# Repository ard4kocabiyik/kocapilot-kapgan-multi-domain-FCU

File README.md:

# Kocapilot Kapgan — Donanım Senkronizasyonlu Uçuş Kontrol Kartı

Kapgan; açık kaynak otopilot yazılımını çalıştıran mikrodenetleyicili uçuş kontrolcüsünü ve Linux tabanlı yardımcı bilgisayarı (YB) tek kart yığınında birleştiren, iki saati ayrılmış bir donanım senkron hattıyla ilişkilendiren bir uçuş kontrol kartıdır. Amaç, İHA'da kaydedilen video karelerini uçuş telemetrisiyle (konum, irtifa, yönelim) milisaniyenin altına yakın doğrulukla eşlemek ve bu doğruluğu kamera görüş alanındaki bir LED ile ölçerek raporlamaktır.

Bu depo, TÜBİTAK 2209-A (2026 yılı 1. dönem) başvurusuna konu olan projenin tasarım dosyalarını, devre benzetim modellerini ve teknik raporlarını içerir.

> **Durum (Kasım 2026):** Rev-A şeması ve 4 katmanlı PCB yerleşimi tamamlandı; güç ağı ve SPI sinyal bütünlüğü benzetimleri yapıldı. Rev-A henüz üretilmedi. Ölçüm ve uçuş sonuçları proje süresince bu depoya eklenecektir.

---

## Depo içeriği

| Klasör / dosya | İçerik |
|---|---|
| `.kicad_pro`, `.kicad_sch`, `.kicad_pcb` | KiCad proje, şema ve PCB dosyaları (Rev-A) |
| `ibom.html` | Etkileşimli malzeme listesi; tarayıcıda açılır, dizgi sırasında kullanılır |
| `kocapilot Kapgan.step` | Kartın 3B modeli |
| `kapgan_case.step` | Kartın kutu modeli |
| `Ltspice/Kapgan_Guc_Agi.asc` | Güç ağı benzetimi (5 V giriş, 3,3 V regülatör açılışı) |
| `Ltspice/Kapgan_SPI_SI.asc` | Mikrodenetleyici–IMU SPI hattı sinyal bütünlüğü benzetimi |
| `Docs/Kocapilot_Kapgan_SCH_Raporu.pdf` | Şema tasarım ve inceleme raporu |
| `Docs/Kapgan_Guc_Agi_Simulasyon_Raporu.pdf` | Güç ağı benzetim raporu |
| `Docs/Kapgan_SPI_SI_Simulasyon_Raporu.pdf` | SPI sinyal bütünlüğü benzetim raporu |
| `Docs/Literatür-Taraması.pdf` | Literatür taraması |

## Kart özeti

- 168 MHz, FPU'lu ARM Cortex-M4F çekirdekli 32-bit mikrodenetleyici
- Ayrı SPI hatlarında, farklı üreticilere ait iki adet 6 eksenli MEMS IMU
- I2C arayüzlü MEMS barometrik basınç sensörü
- SPI üzerinden microSD kayıt, CAN alıcı-verici, motor çıkışları
- Linux tabanlı tek kartlı bilgisayara (YB) takılan 40 pinli genişleme bağlantısı
- 4 katmanlı baskı devre kartı
- Besleme: harici 5 V ve USB-C girişleri diyotla birleştirilir; sensör beslemeleri ferrit boncuklarla dijital hattan ayrılır
- YB ile kart arasındaki seri hat ve senkron hattı tampon entegrelerinden geçer; YB kapalıyken bu hatlar yüksek empedansa geçer
- Uçuş kontrolü ayrı mikrodenetleyicide çalıştığı için kart, YB takılı olmadan da otopilot olarak çalışır

## Senkronizasyon yöntemi

1. Mikrodenetleyici, otopilot yazılımının kamera tetikleme işlevi üzerinden saniyede bir senkron darbesi üretir.
2. Aynı darbe, kesme destekli bir geri besleme girişine geri bağlanır; otopilot yazılımı darbenin kendi saatine göre zamanını kaydeder ve MAVLink `CAMERA_FEEDBACK` mesajıyla YB'ye gönderir.
3. YB, darbenin yükselen kenarını Linux GPIO karakter aygıtı arayüzüyle kendi saatine göre zaman damgalar.
4. Darbe çiftlerinden iki saat arasındaki fark ve kayma (sabit fark + doğrusal kayma modeli) kestirilir; her video karesinin zamanı uçuş kontrolcüsü saatine çevrilerek konum ve yönelim ara değerlemeyle bulunur.

Otopilot yazılımının kaynak kodu değiştirilmez; yalnızca kart tanım dosyaları ve parametreler kullanılır.

Eşleme doğruluğu üç yöntemle karşılaştırılır: **K1** telemetri mesajının YB'ye varış zamanı, **K2** yalnızca MAVLink zaman eşleme protokolü, **K3** protokol + donanım senkron darbesi (önerilen yöntem). Gerçek değer, kamera görüş alanındaki ve pin kenarından zaman damgalanan bir LED ile ölçülür.

## Benzetim sonuçları (özet)

| Benzetim | Sonuç |
|---|---|
| Güç ağı | 3,3 V hattı aşım olmadan yaklaşık 3 ms'de oturuyor; açılış tepe akımları sigorta tutma akımlarının altında |
| SPI sinyal bütünlüğü | Örneklenen tüm bitler lojik eşikleri sağlıyor |

Ayrıntılar `Docs/` klasöründeki raporlardadır. Benzetim sonuçları Rev-A üzerinde osiloskop ölçümleriyle karşılaştırılacaktır.

## Yol haritası

| İş paketi | Kapsam |
|---|---|
| İP1 | Rev-A üretimi, dizgi, ilk enerji; kart tanım dosyaları ve otopilot yazılımının yüklenmesi |
| İP2 | YB kayıt servisi, senkron darbesi, saat modeli ve eşleme yazılımı |
| İP3 | Elektriksel ölçümler, tetik gecikmesi ölçümü, masaüstü senkron deneyleri (K1–K3), Rev-B tasarımı |
| İP4 | Rev-B üretimi, uçuş platformunun kurulumu, pervanesiz ve iple bağlı testler |
| İP5 | Pilot kontrolünde, görerek yapılan uçuşlar ve uçuş içi senkron ölçümleri |
| İP6 | İstatistiksel analiz ve veri setinin yayımlanması |

## Ekip

- Arda Kocabıyık — proje yürütücüsü
- Ali Demirci
- Efe Haskuka

Akademik danışman: Sibel Yenikaya — Bursa Uludağ Üniversitesi, Elektrik-Elektronik Mühendisliği Bölümü

## Atıf

A. Kocabıyık, A. Demirci ve E. Haskuka, "Uçuş kontrol kartı tasarım dosyaları, devre benzetim modelleri ve teknik raporlar," GitHub deposu, 2026. https://github.com/ard4kocabiyik/kocapilot-kapgan-multi-domain-FCU

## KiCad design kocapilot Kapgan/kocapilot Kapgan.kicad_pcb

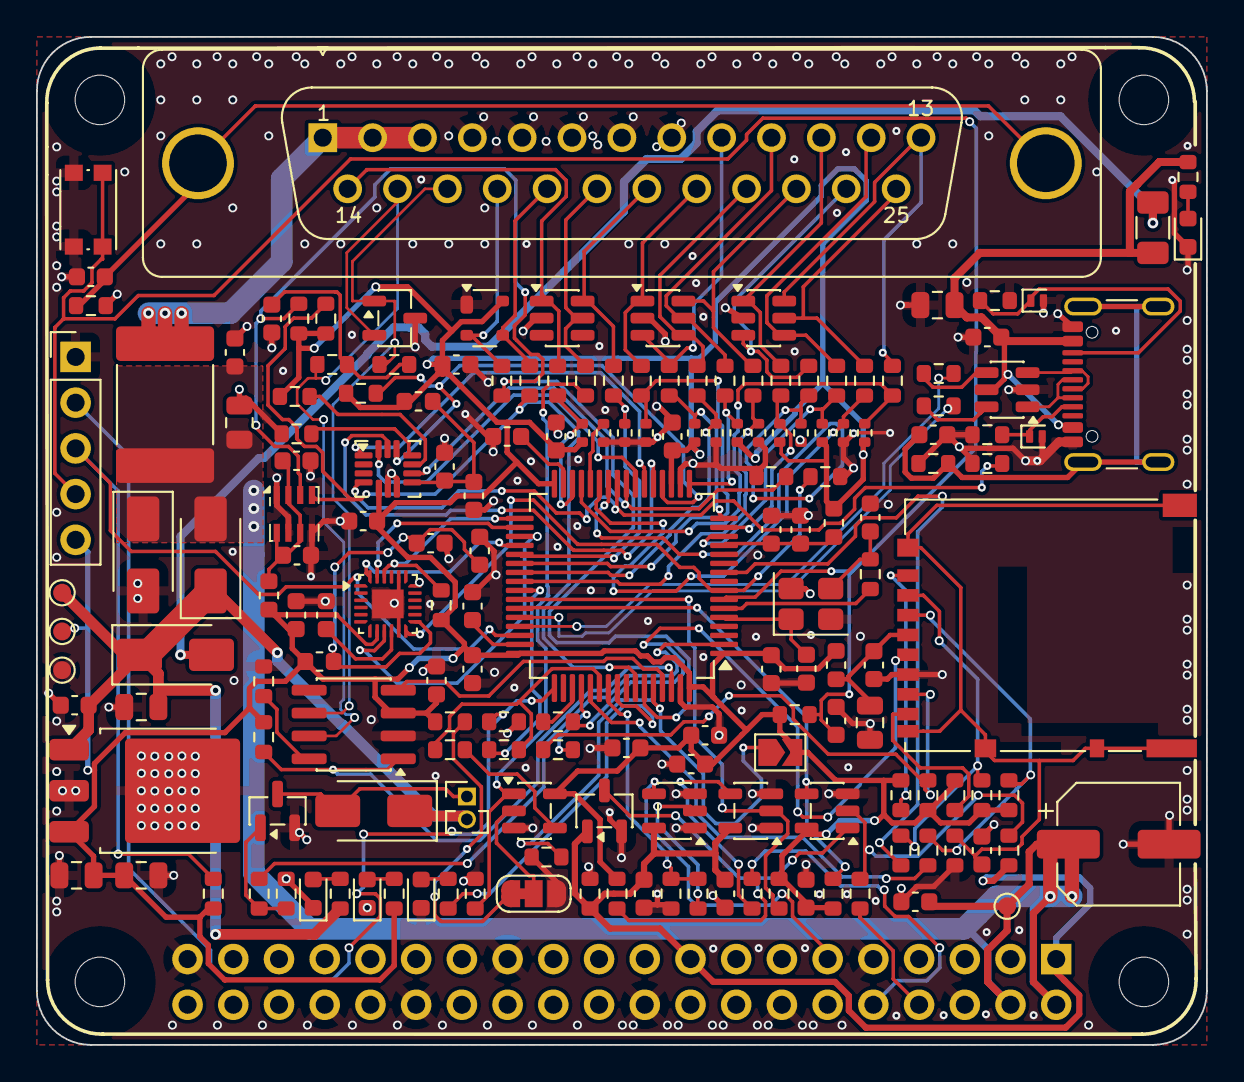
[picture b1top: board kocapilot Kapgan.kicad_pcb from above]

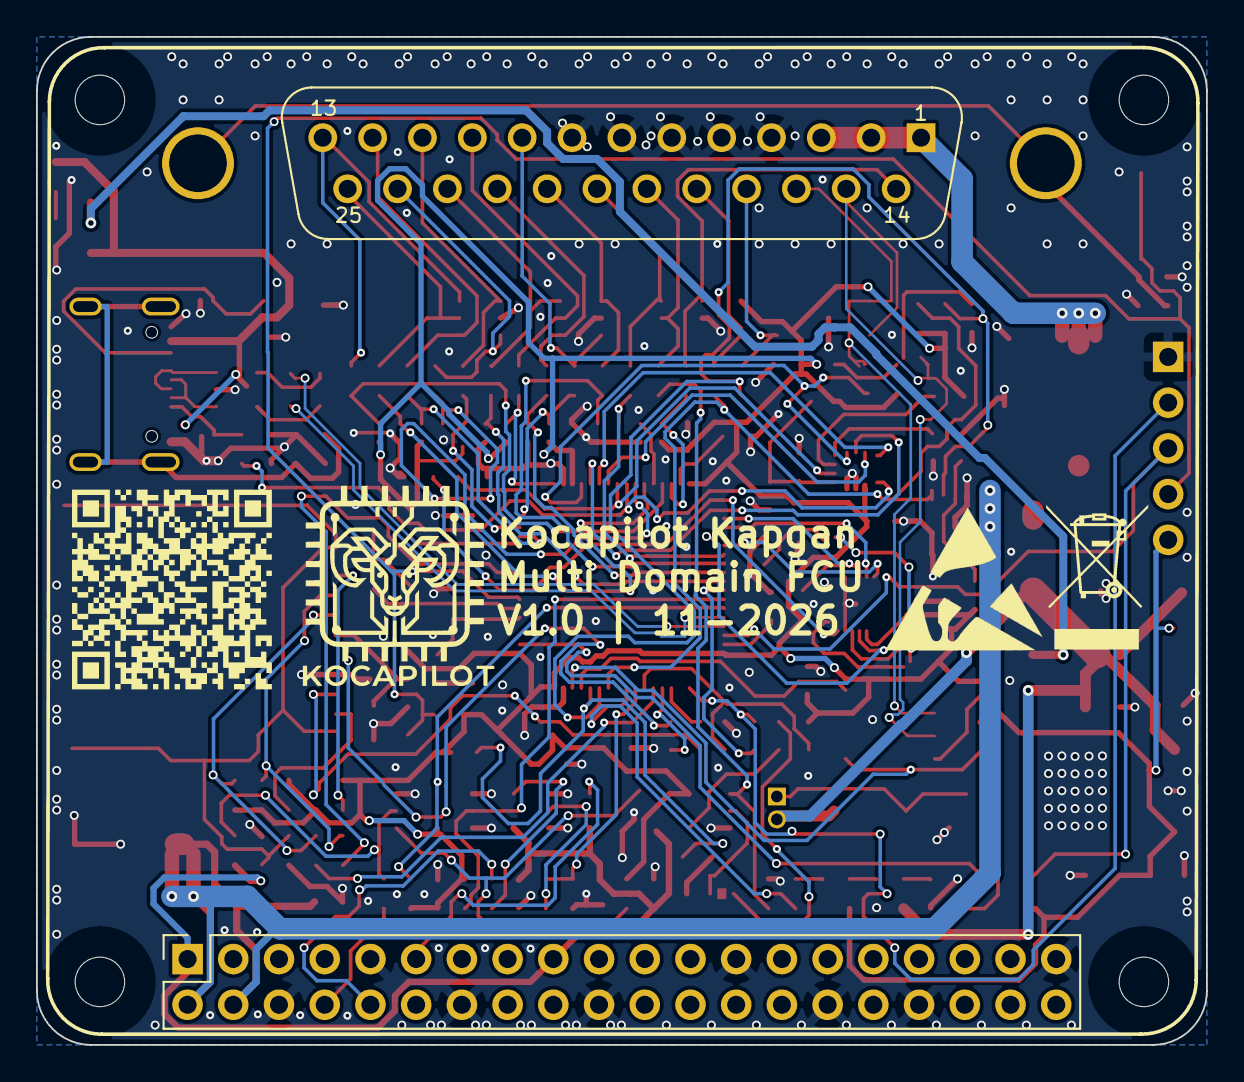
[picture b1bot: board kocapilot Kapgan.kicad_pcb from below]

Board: 4 copper layers, 65.0 x 56.0 mm, 181 parts (4 on the bottom side), 117 nets.

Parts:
C1, C2, C37, C43: 4.7n; C_0603_1608Metric
C3, C5, C7, C10, C11, C12, C14, C16, C18, C20, C21, C22, C23, C24, C25, C27, C28, C30, C31, C33, C34, C35, C40, C42, C44: 0.1u; C_0603_1608Metric
C4, C29: 4.7u; C_0805_2012Metric
C6, C8, C9, C38: 10u; C_0805_2012Metric
C13, C17, C36: 1u; C_0603_1608Metric
C15, C19: 2.2U; C_0603_1608Metric
C26: 10n; C_0603_1608Metric
C32, C39: 12p; C_0603_1608Metric
C41: 100u/16v; CP_Elec_6.3x5.4
CR1: PESD2CAN_215; SOT-23-3
D1: SMAJ6.0A; D_SMA
D2, D3, D7: SS34; D_SMA
D4, D6, D13: ESDA6V1-5SC6; SOT-23-6
D5: PRTR5V0U2X; SOT-143
D8: LED_RED_5V; LED_0603_1608Metric
D9: LED_BLUE_STATUS; LED_0603_1608Metric
D10: LED_GREEN_3V3; LED_0603_1608Metric
D11: LED_AMBER_VBUS; LED_0603_1608Metric
D12, D14: PESD5V0S1UL; D_SOD-882
F1: 2A PTC; Fuse_2920_7451Metric
F2: 1A PTC; Fuse_1206_3216Metric
FB1, FB2, FB3, FB4, FB5: BLM18EG601SN1D; L_0603_1608Metric
H1, H2, H3, H4: M2.5_Mount; MountingHole_2.75mm_M2.5_HAT
J1: SWD; PinHeader_1x05_P2.54mm_Vertical
J2: DB25_Pins_MountingHoles; DSUB-25_Pins_Vertical_P2.77x2.84mm_MountingHoles
J3: Conn_01x02_Pin; PinHeader_1x02_P1.27mm_Vertical
J4: USB_C_Receptacle_USB2.0_16P; USB_C_Receptacle_GCT_USB4105-xx-A_16P_TopMnt_Horizontal
J5: Micro_SD_Card; microSD_HC_Hirose_DM3AT-SF-PEJM5
J6: Raspberry_Pi_Zero_2W; PinSocket_2x20_P2.54mm_Vertical
JP1: SolderJumper_3_Bridged12; SolderJumper-3_P1.3mm_Bridged12_RoundedPad1.0x1.5mm_NumberL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
JP2: SolderJumper_2_Open; SolderJumper-2_P1.3mm_Open_TrianglePad1.0x1.5mm
LOGO0: ESD-Logo_8.9x8mm_SilkScreen
LOGO1: WEEE-Logo_5.6x8mm_SilkScreen
Q1: AO3400A; SOT-23
Q2: 2N7002; SOT-23-3
R1, R61, R72: 1M; R_0603_1608Metric
R2: 0; R_0603_1608Metric
R3, R16: 2.2K; R_0603_1608Metric
R4, R6, R7, R10, R14, R18, R27, R29, R33, R35, R38, R53, R54, R62, R65, R69, R70, R73, R75, R78, R80: 10K; R_0603_1608Metric
R5, R15: 1K; R_0603_1608Metric
R8, R28: 60.4; R_0603_1608Metric
R9, R34, R47, R79: 100; R_0603_1608Metric
R11: 0_DNP; R_0603_1608Metric
R12, R19, R20, R21, R22, R45, R49, R50, R56, R59, R66, R68: 150; R_0603_1608Metric
R13: 10; R_0603_1608Metric
R17, R25, R26, R30, R31, R46, R48, R51, R52, R55, R57, R63, R64: 10K; R_0402_1005Metric
R23, R24, R32, R58, R60, R76, R77: 22; R_0603_1608Metric
R36, R37, R43, R81: 330; R_0603_1608Metric
R39: 470; R_0603_1608Metric
R40, R42: 100k; R_0603_1608Metric
R41, R71, R74: 10k; R_0603_1608Metric
R44, R67: 5.1K; R_0603_1608Metric
README: kapgan_qr
SW1: SW_Push; SW_Push_1P1T_NO_CK_KMR2
TP1: GND; TestPoint_Pad_D1.0mm
TP2: +5V; TestPoint_Pad_D1.0mm
TP3: 3v3; TestPoint_Pad_D1.0mm
TP4: 5V1; TestPoint_Pad_D1.0mm
U1: LD39150DT33; TO-252-3_TabPin2
U2: STM32F405RGTx; LQFP-64_10x10mm_P0.5mm
U3: BMP280; Bosch_LGA-8_2x2.5mm_P0.65mm_ClockwisePinNumbering
U4: MPU-6500; QFN-24-1EP_3x3mm_P0.4mm_EP1.75x1.6mm
U5: BMI270; LGA-14_3x2.5mm_P0.5mm_LayoutBorder3x4y
U6: 74LVC1G86; SOT-23-5
U7, U10, U11: 74LVC1G125; SOT-23-5
U8: SN65HVD230; SOIC-8_3.9x4.9mm_P1.27mm
U9: USBLC6-2SC6; SOT-23-6
Y1: ABM8-8.000MHZ-10-B2-T; Crystal_SMD_3225-4Pin_3.2x2.5mm

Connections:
3.3V_DIGI: C7.1, C8.1, C9.2, C10.2, C14.2, C16.1, C18.1, C20.1, C21.1, C22.2, C24.1, C28.2, C34.1, C40.2, D5.4 (VCC), FB1.2, FB2.1, FB3.1, FB4.1, FB5.2, J1.5, JP2.2 (B), R3.1, R4.2, R6.1, R14.1, R16.1, R26.2, R27.2, R29.1, R31.2, R33.2, R42.2, R43.1, R51.2, R52.2, R53.1, R55.2, R57.2, R69.1, R70.1, R73.1, R74.1, R75.2, R78.2, R80.2, TP3.1, U1.3 (VO), U2.1 (VBAT), U2.19 (VDD), U2.32 (VDD), U2.48 (VDD), U2.64 (VDD), U4.8 (VDDIO), U5.5 (VDDIO), U6.5 (VCC), U8.3 (VCC), U10.5 (VCC)
5V1: C5.2, C6.2, C41.1, C42.2, D1.1 (A1), D2.2 (A), F1.1, J6.2 (5V), J6.4 (5V), TP4.1
+5V: C3.2, C4.2, D2.1 (K), D3.1 (K), D7.1 (K), J3.2, R37.1, TP2.1, U1.1 (VI)
/BMI270_INT1: R54.2, U2.25 (PC5), U5.4 (INT1)
/BMI270_INT2: R62.2, U2.24 (PC4), U5.9 (INT2)
/BUZZER: R5.2, U2.2 (PC13)
/BUZZER_GND: D7.2 (A), J3.1, Q1.3 (D)
/CAN1_RX: U2.61 (PB8), U8.4 (R)
/MCU_LED: R36.1, U2.56 (PB4)
/MPU_INT: R65.1, U2.8 (PC0), U4.12 (INT)
/NRST: C35.1, J1.4, R53.2, SW1.2, U2.7 (NRST)
/OSC_IN: C39.1, U2.5 (PH0), Y1.1
/OSC_OUT: R47.1, U2.6 (PH1)
/RC_IN_UART: R11.2, R15.1, U2.54 (PD2)
/SPI1_MISO: U2.22 (PA6), U5.1 (SDO)
/SPI1_MOSI: U2.23 (PA7), U5.14 (SDX)
/SPI1_NSS: R14.2, U2.20 (PA4), U5.12 (CSB)
/SPI1_SCK: U2.21 (PA5), U5.13 (SCX)
/SPI2_MISO: U2.35 (PB14), U4.9 (SDO/ADO)
/SPI2_MOSI: U2.36 (PB15), U4.24 (SDA/SDI)
/SPI2_NSS: R27.1, U2.33 (PB12), U4.22 (nCS)
/SPI2_SCK: U2.34 (PB13), U4.23 (SCL/SCLK)
/SWCLK: J1.2, R10.1, U2.49 (PA14)
/SWDIO: J1.3, R6.2, U2.46 (PA13)
/USB_DN: R58.2, U2.44 (PA11)
/USB_DP: R60.2, U2.45 (PA12)
/VBUS: C29.2, C31.2, F2.1, J4.A4 (VBUS), J4.A9 (VBUS), J4.B4 (VBUS), J4.B9 (VBUS), R81.1, U9.5 (VBUS)
CAN1_TX: R4.1, U2.62 (PB9), U8.1 (D)
CAN_N: CR1.1, J2.16, R8.2, U8.6 (CANL)
CAN_P: CR1.2, J2.15, R28.1, U8.7 (CANH)
GND: C1.1, C2.1, C3.1, C4.1, C5.1, C6.1, C7.2, C8.2, C9.1, C10.1, C11.2, C12.1, C13.2, C14.1, C15.1, C16.2, C17.2, C18.2, C19.1, C20.2, C21.2, C22.1, C23.1, C24.2, C25.1, C26.2, C27.2, C28.1, C29.1, C30.1, C31.1, C32.2, C33.1, C34.2, C35.2, C36.1, C37.2, C38.1, C39.2, C40.1, C41.2, C42.1, C43.2, C44.2, CR1.3, D1.2 (A2), D4.2 (GND), D5.1 (GND), D6.2 (GND), D8.1 (K), D9.1 (K), D10.1 (K), D11.1 (K), D12.2 (A), D13.2 (GND), D14.2 (A), J1.1, J2.4, J2.5, J2.6, J2.7, J2.8, J4.A1 (GND), J4.A12 (GND), J4.B1 (GND), J4.B12 (GND), J5.6 (VSS), J6.6 (GND), J6.9 (GND), J6.14 (GND), J6.20 (GND), J6.25 (GND), J6.30 (GND), J6.34 (GND), J6.39 (GND), JP1.3 (B), Q1.2 (S), Q2.2 (S), R1.2, R2.2, R7.2, R10.2, R17.2, R18.1, R25.2, R30.2, R35.1, R38.2, R40.2, R41.1, R44.2, R46.2, R48.2, R54.1, R61.1, R62.1, R63.2, R64.2, R65.2, R67.1, R72.1, SW1.1, TP1.1, U1.2 (GND), U2.12 (VSSA), U2.18 (VSS), U2.63 (VSS), U3.1 (GND), U3.5 (SDO), U3.7 (GND), U4.11 (FSYNC), U4.18 (GND), U4.20 (RESV), U4.25, U5.6 (GNDIO), U5.7 (GND), U6.3 (GND), U7.1, U7.3 (GND), U8.2 (GND), U9.2 (GND), U10.3 (GND), U11.1, U11.3 (GND), Y1.2, Y1.4
GPIO_MCU: R39.2, R41.2, U2.55 (PB3)
GPIO_ZERO: J6.11 (GPIO17), U7.4
I2C1_SCL: R16.2, R23.2, U2.58 (PB6), U3.4 (SCK)
I2C1_SDA: R3.2, R32.2, U2.59 (PB7), U3.3 (SDI)
unnamed: C32.1, R47.2, Y1.3
unnamed: C2.2, R8.1, R28.2
unnamed: C43.1, J5.9 (SHIELD), J5.10 (SHIELD), J5.11 (SHIELD), R72.2
unnamed: D14.1 (K), J4.A5 (CC1), R67.2
unnamed: D9.2 (A), R36.2
unnamed: D11.2 (A), R81.2
unnamed: D8.2 (A), R37.2
unnamed: D10.2 (A), R43.2
unnamed: D12.1 (K), J4.B5 (CC2), R44.1
unnamed: D3.2 (A), F2.2
unnamed: D5.2 (I/O1), J2.17, R32.1
unnamed: D5.3 (I/O2), J2.18, R23.1
unnamed: D6.1 (IO1), J2.14, R9.1
unnamed: D6.5 (IO4), J2.19, R19.1
unnamed: D6.6 (IO5), J2.20, R22.1
unnamed: D4.1 (IO1), J2.21, R21.1
unnamed: D4.3 (IO2), J2.9, R12.1
unnamed: D4.4 (IO3), J2.22, R20.1
unnamed: D4.5 (IO4), J2.10, R68.1
unnamed: D4.6 (IO5), J2.23, R66.1
unnamed: D13.1 (IO1), J2.11, R50.1
unnamed: D13.3 (IO2), J2.24, R56.1
unnamed: D13.4 (IO3), J2.12, R59.1
unnamed: D13.5 (IO4), J2.25, R49.1
unnamed: D13.6 (IO5), J2.13, R45.1
unnamed: F1.2, J2.1, J2.2, J2.3
unnamed: J6.8 (GPIO14/TXD), R79.1
unnamed: J6.10 (GPIO15/RXD), R34.2
unnamed: J4.A6 (D+), J4.B6 (D+), U9.3 (I/O2)
unnamed: J4.A7 (D-), J4.B7 (D-), U9.1 (I/O1)
unnamed: C37.1, J4.S1 (SHIELD), R61.2
unnamed: J5.5 (CLK), R24.2
unnamed: J5.3 (CMD), R69.2, R76.2
unnamed: J5.7 (DAT0), R13.1, R73.2
unnamed: J5.8 (DAT1), R75.1
unnamed: J5.1 (DAT2), R78.1
unnamed: J5.2 (DAT3/CD), R70.2, R77.2
unnamed: C30.2, C38.2, FB5.1, J5.4 (VDD)
unnamed: C1.2, J2.0 (PAD), R1.1
unnamed: JP2.1 (A), R35.2, U2.60 (BOOT0)
unnamed: JP1.1 (A), R29.2
unnamed: JP1.2 (C), U6.2
unnamed: Q1.1 (G), R5.1, R7.1
unnamed: Q2.3 (D), R42.1, U10.1
unnamed: R58.1, U9.6 (I/O1)
unnamed: R60.1, U9.4 (I/O2)
unnamed: R15.2, U6.4
unnamed: R39.1, U7.2
unnamed: R33.1, U5.10 (OCSB)
unnamed: R18.2, U5.11 (OSDO)
unnamed: C11.1, C13.1, FB2.2, U5.8 (VDD)
unnamed: C25.2, U4.10 (REGOUT)
unnamed: C17.1, C26.1, FB3.2, U4.13 (VDD)
unnamed: R11.1, U2.41 (PA8)
unnamed: R17.1, U2.28 (PB2)
unnamed: C19.2, U2.31 (VCAP_1)
unnamed: C15.2, U2.47 (VCAP_2)
unnamed: C33.2, C36.2, FB4.2, U2.13 (VDDA)
unnamed: C12.2, C23.2, FB1.1, U3.2 (CSB), U3.6 (VDD), U3.8 (VDDIO)
unnamed: R2.1, U8.8 (Rs)
PI_3V3: C27.1, C44.1, J6.1 (3V3), J6.17 (3V3), Q2.1 (G), R40.1, R71.1, U7.5 (VCC), U11.5 (VCC)
PI_RX: R34.1, U11.4
PI_TX: R71.2, R79.2, U10.2
RC_IN: R19.2, R38.1, U6.1
SD_NSS: R77.1, U2.10 (PC2)
SPI3_MISO: R13.2, U2.52 (PC11)
SPI3_MOSI: R76.1, U2.53 (PC12)
SPI3_SCK: R24.1, U2.51 (PC10)
TIM3_CH3: R46.1, R56.2, U2.26 (PB0)
TIM3_CH4: R48.1, R49.2, U2.27 (PB1)
TIM8_CH1: R22.2, R25.1, U2.37 (PC6)
TIM8_CH2: R21.2, R30.1, U2.38 (PC7)
TIM8_CH3: R20.2, R63.1, U2.39 (PC8)
TIM8_CH4: R64.1, R66.2, U2.40 (PC9)
USART1_RX: R74.2, U2.43 (PA10), U10.4
USART1_TX: R80.1, U2.42 (PA9), U11.2
USART2_CTS: R57.1, R59.2, U2.14 (PA0)
USART2_RTS: R50.2, R51.1, U2.15 (PA1)
USART2_RX: R55.1, R68.2, U2.17 (PA3)
USART2_TX: R12.2, R31.1, U2.16 (PA2)
USART3_RX: R9.2, R26.1, U2.30 (PB11)
USART3_TX: R45.2, R52.1, U2.29 (PB10)
